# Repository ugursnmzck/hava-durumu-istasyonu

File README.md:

# Hava Durumu İstasyonu

V2.0 Yapılan Değişiklikler:
- CAD yazılımı olarak Autodesk Eagle bırakılarak KiCAD kullanıldı.
- Mikroişlemci devresinde dijital güç girişlerinin tamamına filtre kondansatörü eklendi.
- Sıcaklık sensörünün çalışmasını engelleyen filtre kondansatörüne ait bağlantı hatası düzeltildi.
- PCB 4 katmanlı olarak yeniden tasarlandı.

V1.0:

Sıcaklık, nem ve basınç verileri sensörler yardımıyla okunarak kablosuz bir şekilde bilgisayara iletilmektedir.

Sıcaklık ve nem sensörü olarak SHT30, basınç sensörü olarak ise BMP280 kullanılmıştır. Mikrodenetleyici olarak STM32F103C8T6 tercih edilmiştir. Sensör verilerinin yanında pil geirlimi ve gerçek zamanlı saat verisi de mikrodenetleyici ile oluşturulmaktadır. Kablosuz haberleşme için ESP8266-01 modülü tercih edilmiştir. Gömülü sistem kodları C dilinde STM32 CubeIDE üzerinde yazılmıştır. Grafik arayüzü Visual Studio üzerinde C# dili ile hazırlanmıştır. Arayüz tasarımında .NET Framework ve SimpleTCP eklentisi gereklidir.

Gerekli PCB tasarımı Autodesk Eagle ile yapılmıştır.

Proje elektrik elektronik mühendisliği lisans bitirme projesi olarak tasarlanmıştır.

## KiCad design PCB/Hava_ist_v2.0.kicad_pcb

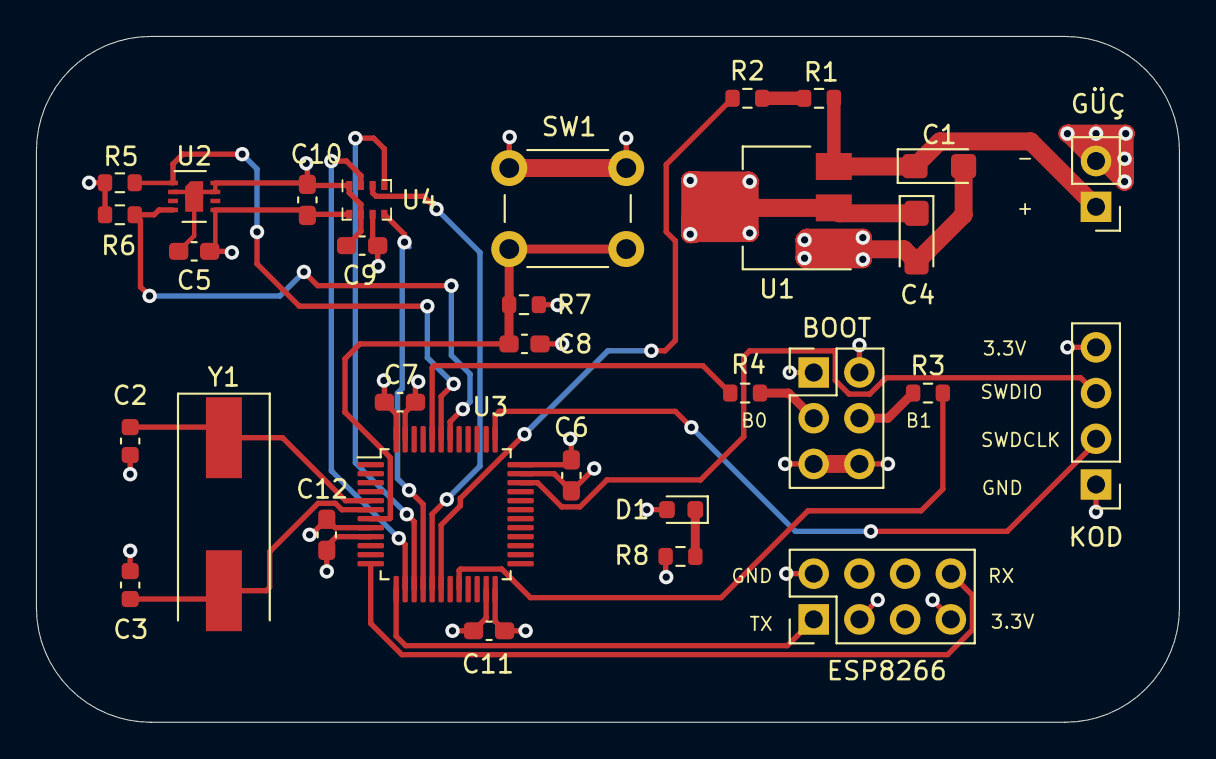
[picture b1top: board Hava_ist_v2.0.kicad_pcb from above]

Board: 4 copper layers, 63.5 x 38.1 mm, 31 parts (0 on the bottom side), 23 nets.

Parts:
BOOT: 2x3; PinHeader_2x03_P2.54mm_Vertical
C1, C4: 10 uF; CP_EIA-3216-18_Kemet-A
C2, C3: 12 pF; C_0603_1608Metric
C5, C6, C7, C8, C9, C10, C11, C12: 100 nF; C_0603_1608Metric_Pad1.08x0.95mm_HandSolder
D1: LED; LED_0603_1608Metric
ESP8266: 2x4; PinHeader_2x04_P2.54mm_Vertical
GÜÇ: 1x2; PinHeader_1x02_P2.54mm_Vertical
KOD: 1x4; PinHeader_1x04_P2.54mm_Vertical
R1, R2: 50k; R_0603_1608Metric
R3, R4: 100k; R_0603_1608Metric
R5, R6, R7: 10k; R_0603_1608Metric
R8: 510 R; R_0603_1608Metric
SW1: SW_Push; SW_PUSH_6mm
U1: AMS1117-3.3; SOT-223-3_TabPin2
U2: SHT30-DIS; Sensirion_DFN-8-1EP_2.5x2.5mm_P0.5mm_EP1.1x1.7mm
U3: STM32F103C8Tx; LQFP-48_7x7mm_P0.5mm
U4: BMP280; Bosch_LGA-8_2x2.5mm_P0.65mm_ClockwisePinNumbering
Y1: 8 MHz; Crystal_SMD_HC49-SD

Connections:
+3V3: BOOT.1, BOOT.2, C4.1, C5.2, C6.1, C7.1, C9.1, C10.1, C11.1, C12.1, D1.2, ESP8266.3, ESP8266.7, KOD.4, R5.1, R6.1, R7.1, U1.2, U2.5, U3.9, U3.24, U3.36, U3.48, U4.6, U4.8
/BOOT0: BOOT.3, R4.2
/BOOT1: BOOT.4, R3.2
/CSB_BMP: U3.14, U4.2
/ESP_RX: ESP8266.8, U3.12
/ESP_TX: ESP8266.1, U3.13
/RESET: C8.1, R7.2, SW1.1, U3.7
/SCK_BMP: U3.15, U4.4
/SCL_SHT: R6.2, U2.4, U3.42
/SDA_SHT: R5.2, U2.1, U3.43
/SDI_BMP: U3.17, U4.3
/SDO_BMP: U3.16, U4.5
/SWDCLK: KOD.2, U3.37
/SWDIO: KOD.3, U3.34
/VIN: C1.1, GÜÇ.1, R1.2, U1.3
GND: BOOT.5, BOOT.6, C1.2, C2.2, C3.2, C4.2, C5.1, C6.2, C7.2, C8.2, C9.2, C10.2, C11.2, C12.2, ESP8266.2, GÜÇ.2, KOD.1, R8.1, SW1.2, U1.1, U2.2, U2.7, U2.8, U2.9, U3.8, U3.23, U3.35, U3.47, U4.1, U4.7
unnamed: C2.1, U3.5, Y1.1
unnamed: C3.1, U3.6, Y1.2
unnamed: D1.1, R8.2
unnamed: R1.1, R2.2
unnamed: R2.1, U3.18
unnamed: R3.1, U3.20
unnamed: R4.1, U3.44

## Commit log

2021-11-04 Create asd
